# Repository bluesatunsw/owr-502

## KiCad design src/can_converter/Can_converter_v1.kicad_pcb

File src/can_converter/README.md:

# Can Converter

USB <-> CANFD Device, based on the upstream CandleLightFD project (STM32G4 variant)

A small USB-C device that allows for the reading of can signals from the rover.

The device uses 5V power from the USB-C port to power, with a buck converter for the 3.3V power on the board. The CAN signals are processed by the TCAN1462V transceiver. The transceiver is connected to the STM32 with data signals RXD, TXD and a standby input. The STM32 also interfaces with two LEDs to display the functionality of the device and actions it's currently performing. CAN signals are processed by the STM32 and sent to the USB-C port to be used for debugging purposes.

# Can Bus Pinout

| Pin | Signal | Colour |
| --- | ------ | ------ |
|  1  | `CANL` | Green  |
|  2  | `CANH` | Yellow |

# Debug Pinout

| Pin | Signal  |
| --- | ------- |
|  1  | `SWDIO` |
|  2  | `SWCLK` |
|  3  | `GND`   |
|  4  | `VDD`   |
|  5  | `SWO`   |
|  6  | `NRST`  |

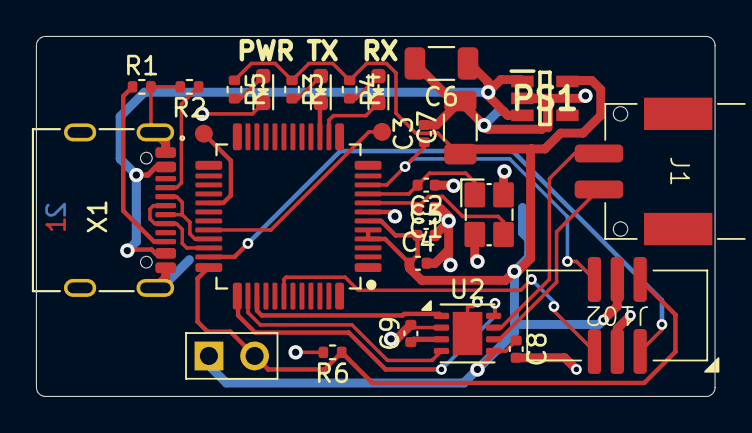
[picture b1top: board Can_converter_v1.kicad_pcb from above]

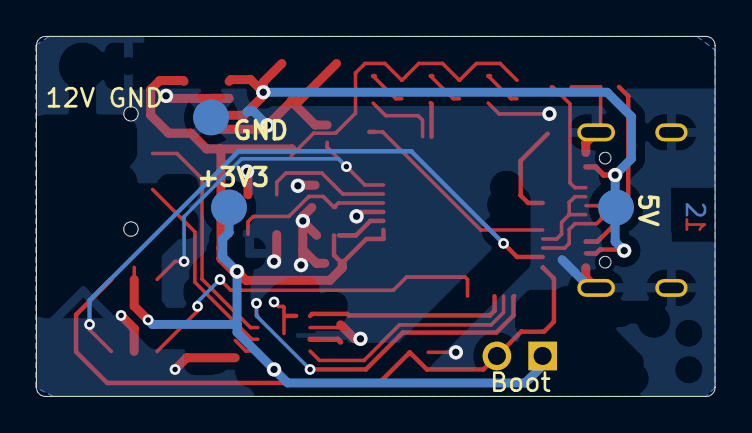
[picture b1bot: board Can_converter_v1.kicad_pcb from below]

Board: 2 copper layers, 37.7 x 20.0 mm, 32 parts (3 on the bottom side), 25 nets.

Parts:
C1, C2: 10p; C_0402_1005Metric
C3, C4, C5, C8, C9: 100n; C_0402_1005Metric
C6, C7: 10u; C_1206_3216Metric
D1, D2: KPT-1608SGC; LED_Kingbright_0603
D3: KPT-1608EC; LED_Kingbright_0603
J1: SM02B-PASS
J102: IDC6
NB2: LAYERSTACK_TB
P2: CONN_01X02; Header_1x2_Pitch2.54mm
PS1: RT9013-33GB; SOT94P279X130-5N
R1, R2: 4K7; R_0402_1005Metric
R3, R4, R5: 1K; R_0402_1005Metric
R6: 10K; R_0402_1005Metric
TP1, TP2, TP3: TP2.0mm
TP4, TP5: TP1.0mm
U1: STM32G0B1CBT; LQFP-48_7mmx7mm_Pitch0.5mm
U2: TCAN1462V; VSON-8-1EP_3x3mm_P0.65mm_EP1.65x2.4mm
X1: 629722000214_pasteInHole; USB4105_pasteInHole
Y1: 830108313809; Crystal_4Pin_SMD_3.2mmx2.5mm

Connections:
+3V3: C4.1, C5.1, C7.1, C8.1, J102.4, P2.1, PS1.5 (VOUT), R3.1, R4.1, R5.1, TP2.1, U1.4 (VBAT), U1.5 (VREF+), U1.6 (VDD/VDDA), U2.5 (VIO)
+5V: C6.1, C9.1, PS1.1 (VIN), PS1.3 (EN), TP1.1, U2.3 (VCC), X1.A4 (VBUS), X1.B4 (VBUS)
/CAN Transceiver/CAN1_H: J1.2, U2.7 (CANH)
/CAN Transceiver/CAN1_L: J1.1, U2.6 (CANL)
/CAN Transceiver/CAN1_RX: U1.38 (PD0), U2.4 (RXD)
/CAN Transceiver/CAN1_S: U1.37 (PA15), U2.8 (STB)
/CAN Transceiver/CAN1_TX: U1.39 (PD1), U2.1 (TXD)
/MCU/LED_RX: D2.2 (K), U1.14 (PA3)
/MCU/LED_TX: D1.2 (K), U1.15 (PA4)
/MCU/NRST: C3.1, J102.6, U1.10 (PF2/NRST)
/MCU/RX: TP4.1, U1.32 (PA10)
/MCU/SWCLK: J102.2, P2.2, R6.1, U1.36 (PA14/BOOT0)
/MCU/SWDIO: J102.1, U1.35 (PA13)
/MCU/SWO: J102.5, U1.42 (PB3)
/MCU/TX: TP5.1, U1.29 (PA9)
/USB_N: U1.33 (PA11[PA9]), X1.A7 (DN1), X1.B7 (DN2)
/USB_P: U1.34 (PA12[PA10]), X1.A6 (DP1), X1.B6 (DP2)
GND: C1.1, C2.1, C3.2, C4.2, C5.2, C6.2, C7.2, C8.2, C9.2, D3.2 (K), J102.3, PS1.2 (GND), R1.2, R2.2, R6.2, TP3.1, U1.7 (VSS/VSSA), U2.2 (GND), U2.9 (EP), X1.A1 (GND), X1.B1 (GND), X1.SH (Shield), Y1.2 (GND), Y1.4 (GND)
unnamed: D1.1 (A), R3.2
unnamed: D2.1 (A), R4.2
unnamed: D3.1 (A), R5.2
unnamed: C1.2, U1.8 (PF0/OSC_IN), Y1.3 (C_{2})
unnamed: C2.2, U1.9 (PF1/OSC_OUT), Y1.1 (C_{1})
unnamed: R2.1, X1.A5 (CC1)
unnamed: R1.1, X1.B5 (CC2)
